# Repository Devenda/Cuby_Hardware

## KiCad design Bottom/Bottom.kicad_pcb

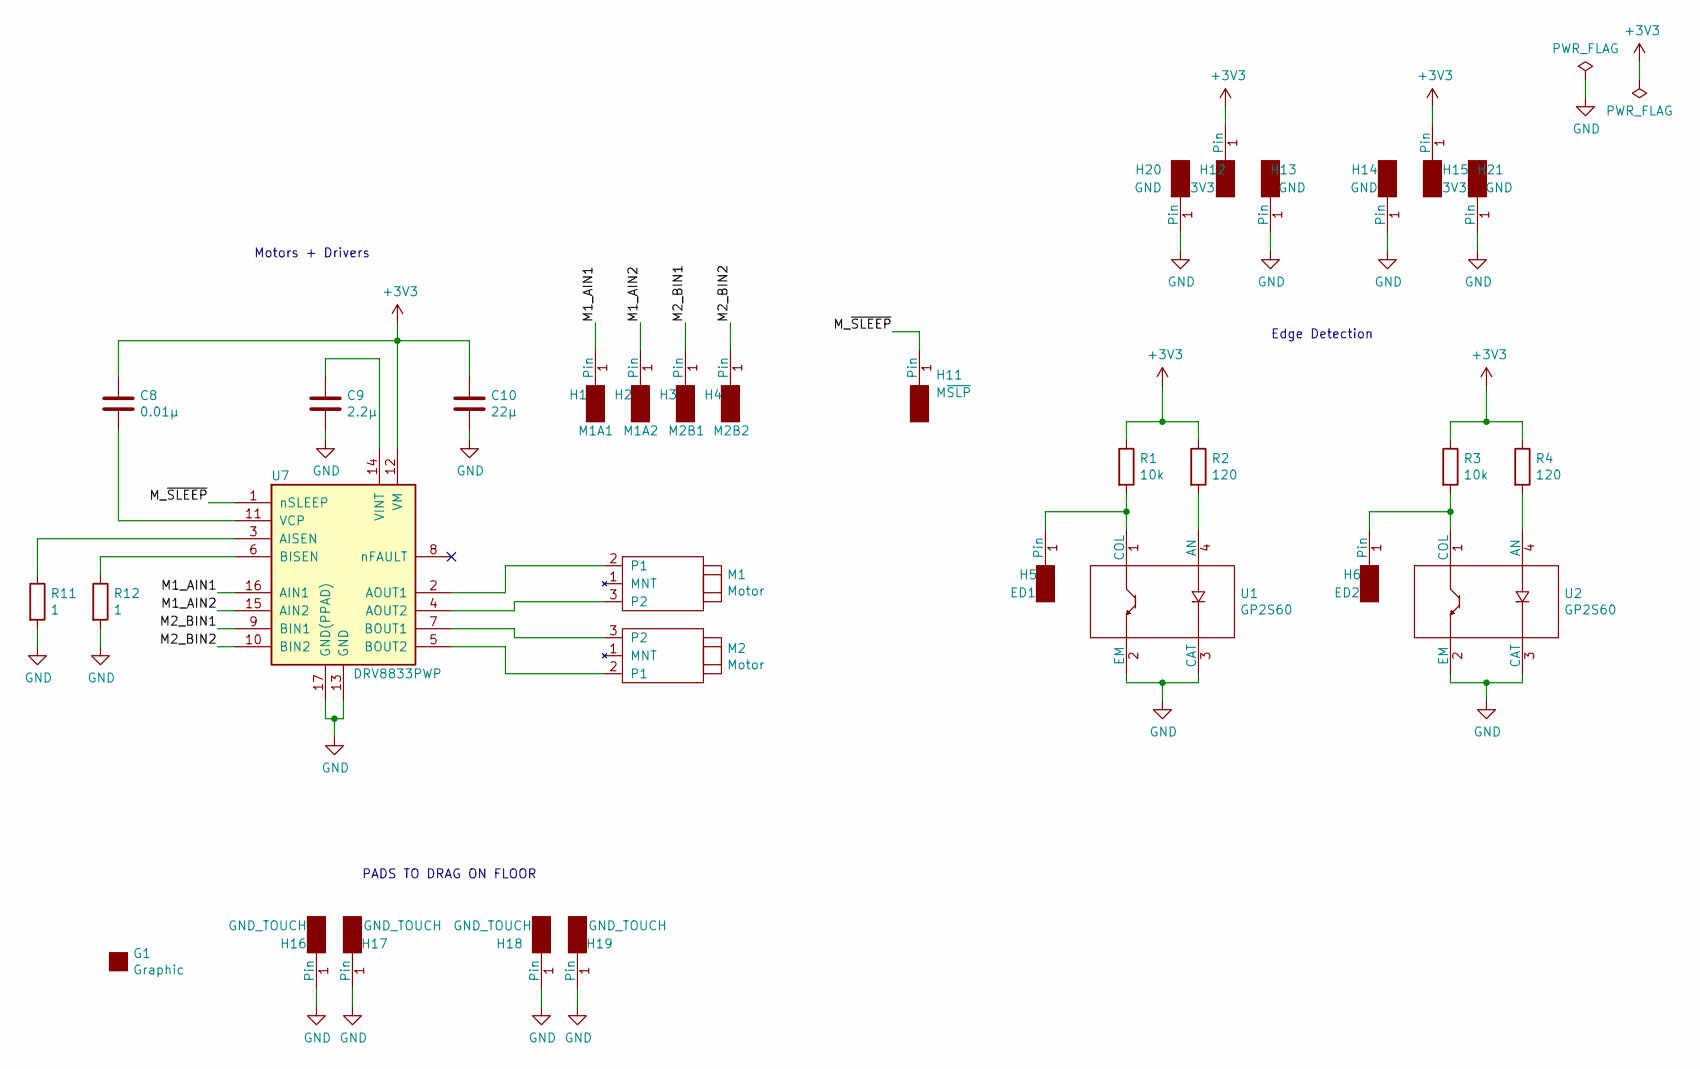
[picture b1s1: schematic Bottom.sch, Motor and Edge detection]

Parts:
C8: 0.01µ; C_0805_2012Metric; LCSC C52278
C9: 2.2µ; C_0805_2012Metric; LCSC C107171
C10: 22µ; C_0805_2012Metric; LCSC C5674
G1: Graphic; d2
H1: M1A1; Mounting_Pad_Signal
H2: M1A2; Mounting_Pad_Signal
H3: M2B1; Mounting_Pad_Signal
H4: M2B2; Mounting_Pad_Signal
H5: ED1; Mounting_Pad_Signal
H6: ED2; Mounting_Pad_Signal
H11: M~SLP; Mounting_Pad_Signal
H12, H15: 3V3; Mounting_Pad_Power
H13, H14, H20, H21: GND; Mounting_Pad_Power
H16, H17, H18, H19: GND_TOUCH; Mounting_Pad_Ground
M1, M2: Motor; Small_DC_Motor
R1, R3: 10k; R_0805_2012Metric; LCSC C38522
R2, R4: 120; R_0805_2012Metric; LCSC C25281
R11, R12: 1; R_0805_2012Metric; LCSC C25288
U1, U2: GP2S60; GP2S60_ReverseMount; LCSC C83485
U7: DRV8833PWP; HTSSOP-16-1EP_4.4x5mm_P0.65mm_EP3.4x5mm_Mask2.46x2.31mm_The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; Farnell 2057085RL

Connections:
+3V3: C8.1, C10.1, H12.1, H15.1, R1.1, R2.1, R3.1, R4.1, U7.12 (VM)
/M1_AIN1: H1.1, U7.16 (AIN1)
/M1_AIN2: H2.1, U7.15 (AIN2)
/M2_BIN1: H3.1, U7.9 (BIN1)
/M2_BIN2: H4.1, U7.10 (BIN2)
/M_~SLEEP: H11.1, U7.1 (nSLEEP)
GND: C9.2, C10.2, H13.1, H14.1, H16.1, H17.1, H18.1, H19.1, H20.1, H21.1, R11.2, R12.2, U1.2 (EM), U1.3 (CAT), U2.2 (EM), U2.3 (CAT), U7.13 (GND), U7.17 (GND(PPAD))
unnamed: C8.2, U7.11 (VCP)
unnamed: C9.1, U7.14 (VINT)
unnamed: H5.1, R1.2, U1.1 (COL)
unnamed: H6.1, R3.2, U2.1 (COL)
unnamed: M1.2 (P1), U7.2 (AOUT1)
unnamed: M1.3 (P2), U7.4 (AOUT2)
unnamed: M2.2 (P1), U7.5 (BOUT2)
unnamed: M2.3 (P2), U7.7 (BOUT1)
unnamed: R2.2, U1.4 (AN)
unnamed: R4.2, U2.4 (AN)
unnamed: R11.1, U7.3 (AISEN)
unnamed: R12.1, U7.6 (BISEN)

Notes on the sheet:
Motors + Drivers
Edge Detection
PADS TO DRAG ON FLOOR

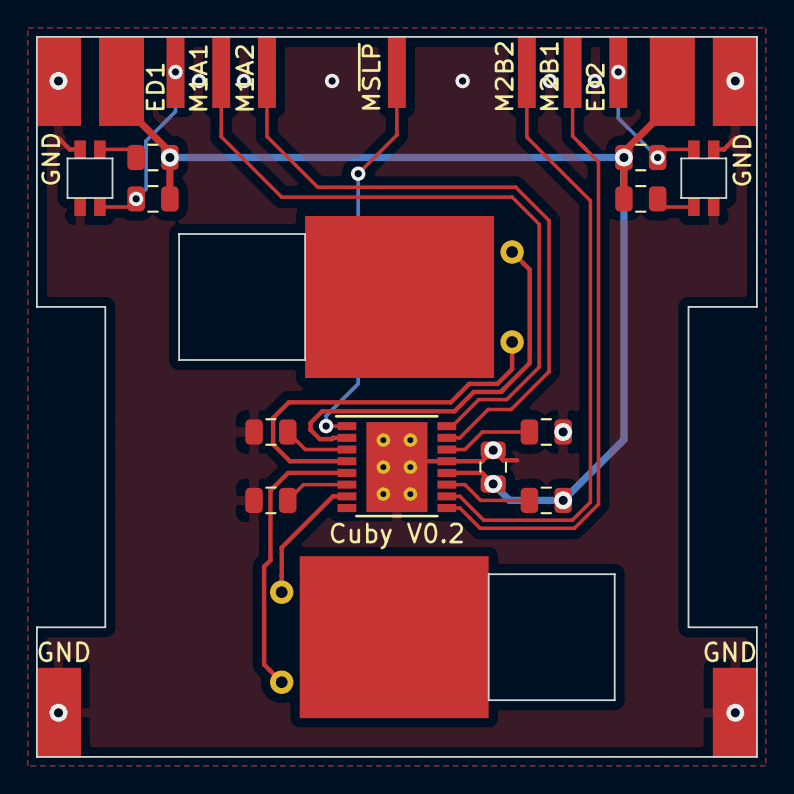
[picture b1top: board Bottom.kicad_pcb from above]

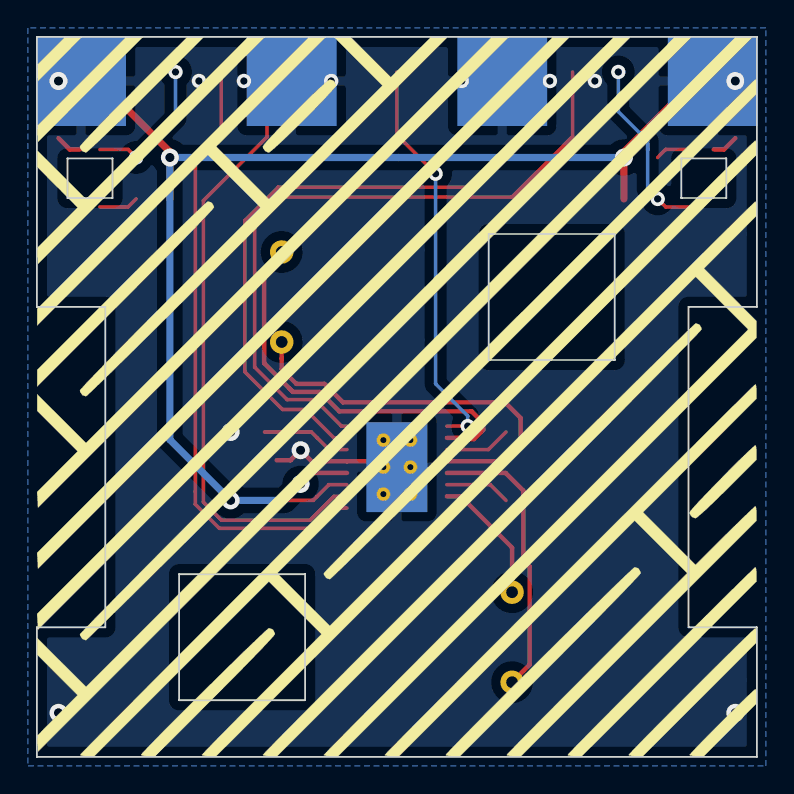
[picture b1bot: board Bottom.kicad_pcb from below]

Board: 2 copper layers, 40.0 x 40.0 mm, 32 parts (5 on the bottom side), 19 nets.

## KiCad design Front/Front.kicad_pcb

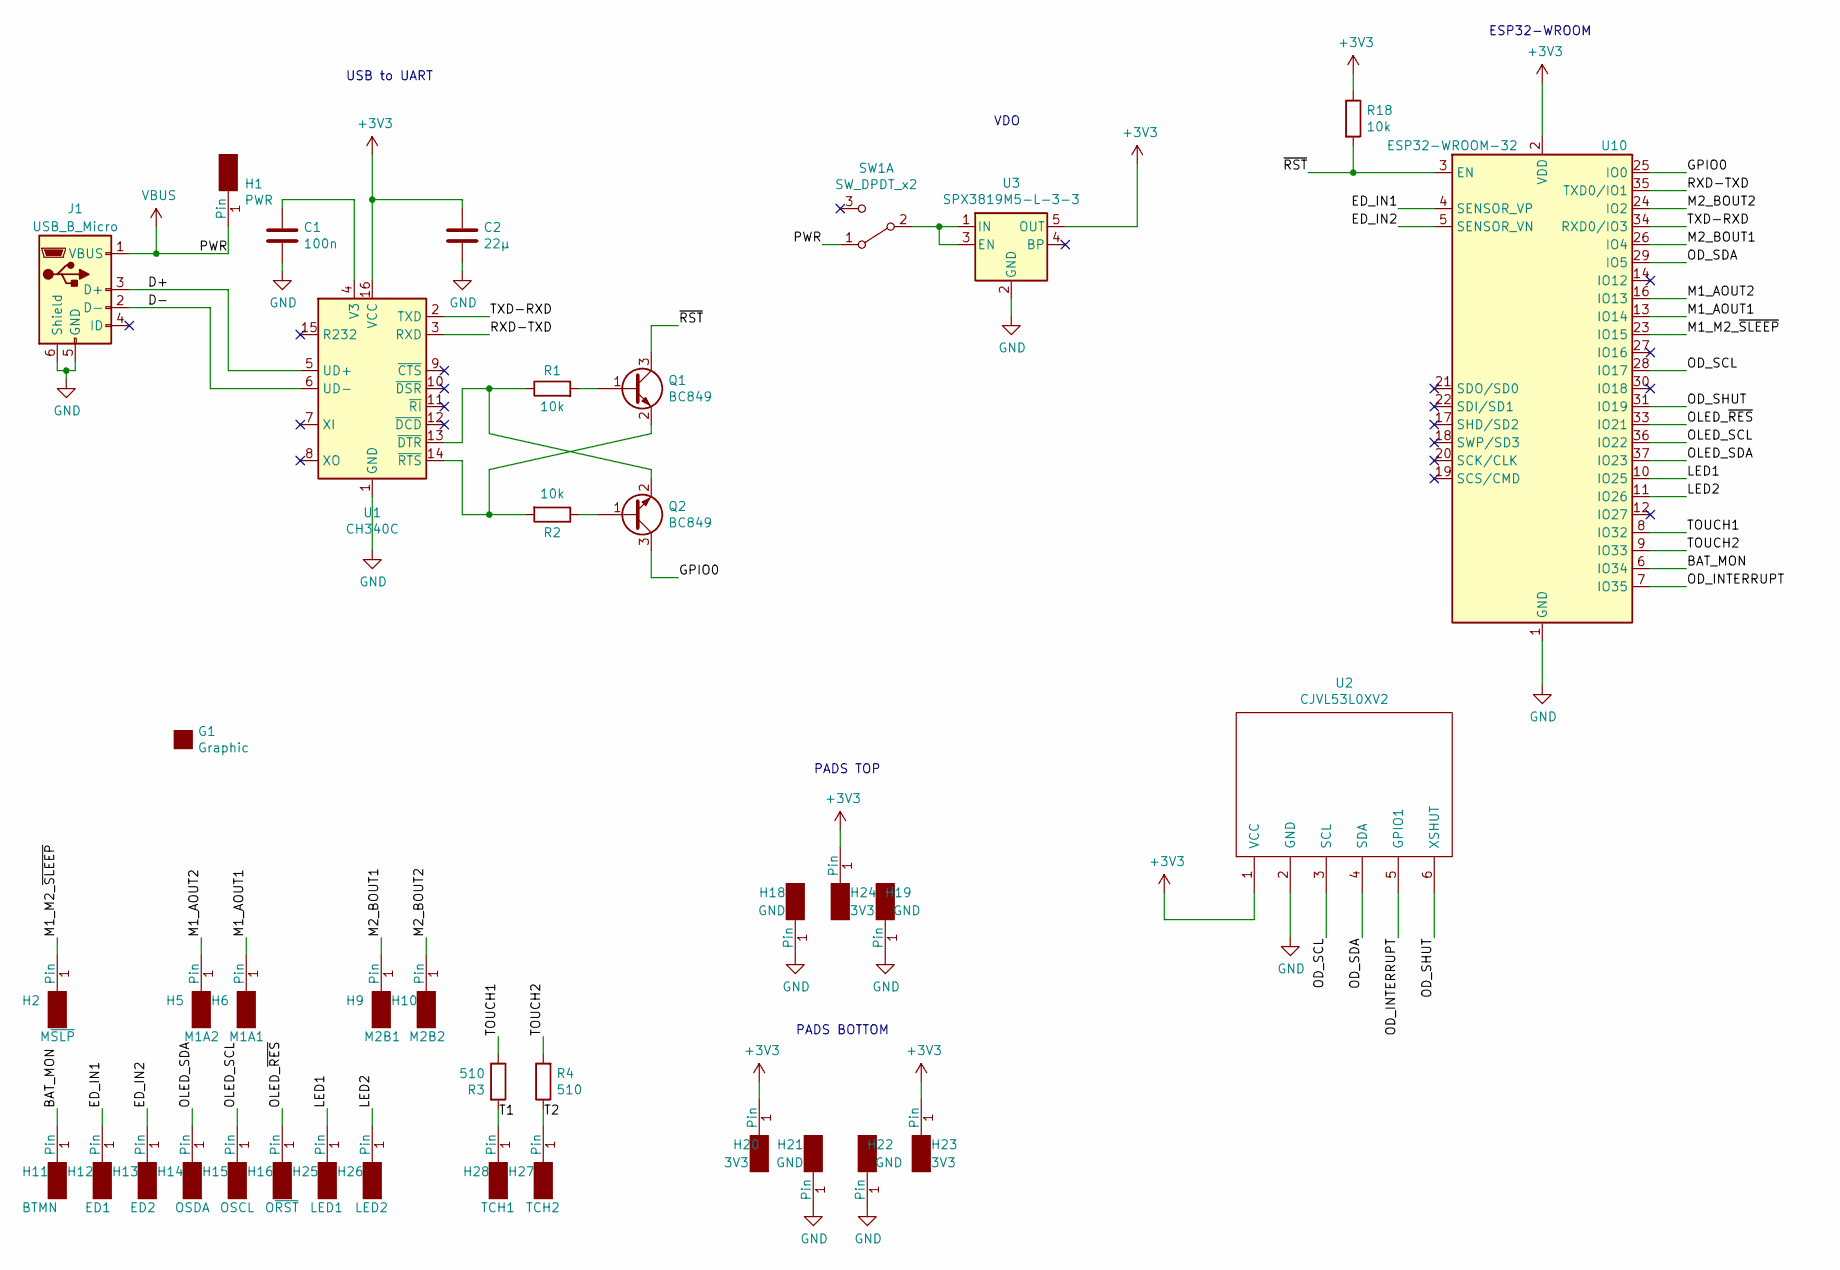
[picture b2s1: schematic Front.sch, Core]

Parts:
C1: 100n; C_0805_2012Metric; LCSC C282732
C2: 22µ; C_0805_2012Metric; LCSC C5674
G1: Graphic; d1
H1: PWR; Mounting_Pad_Power
H2: M~SLP; Mounting_Pad_Signal
H5: M1A2; Mounting_Pad_Signal
H6: M1A1; Mounting_Pad_Signal
H9: M2B1; Mounting_Pad_Signal
H10: M2B2; Mounting_Pad_Signal
H11: BTMN; Mounting_Pad_Signal
H12: ED1; Mounting_Pad_Signal
H13: ED2; Mounting_Pad_Signal
H14: OSDA; Mounting_Pad_Signal
H15: OSCL; Mounting_Pad_Signal
H16: O~RST; Mounting_Pad_Signal
H18, H19, H21, H22: GND; Mounting_Pad_Power
H20, H23, H24: 3V3; Mounting_Pad_Power
H25: LED1; Mounting_Pad_Signal
H26: LED2; Mounting_Pad_Signal
H27: TCH2; Mounting_Pad_Touch
H28: TCH1; Mounting_Pad_Touch
J1: USB_B_Micro; USB_Micro-B_Molex_47346-0001; LCSC C40942
Q1, Q2: BC849; SOT-23; LCSC C163753
R1, R2, R18: 10k; R_0805_2012Metric; LCSC C38522
R3, R4: 510; R_0805_2012Metric; LCSC C25283
SW1: SW_DPDT_x2; JS102011SAQN
U1: CH340C; SOIC-16_3.9x9.9mm_P1.27mm; LCSC C84681
U2: CJVL53L0XV2; GYVL53L0X_NoMountingHoles
U3: SPX3819M5-L-3-3; SOT-23-5; LCSC C9055
U10: ESP32-WROOM-32

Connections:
+3V3: C2.1, H20.1, H23.1, H24.1, R18.1, U1.16 (VCC), U2.1 (VCC), U3.5 (OUT), U10.2 (VDD)
/BAT_MON: H11.1, U10.6 (IO34)
/D+: J1.3 (D+), U1.5 (UD+)
/D-: J1.2 (D-), U1.6 (UD-)
/ED_IN1: H12.1, U10.4 (SENSOR_VP)
/ED_IN2: H13.1, U10.5 (SENSOR_VN)
/GPIO0: Q2.3 (C), U10.25 (IO0)
/LED1: H25.1, U10.10 (IO25)
/LED2: H26.1, U10.11 (IO26)
/M1_AOUT1: H6.1, U10.13 (IO14)
/M1_AOUT2: H5.1, U10.16 (IO13)
/M1_M2_~SLEEP: H2.1, U10.23 (IO15)
/M2_BOUT1: H9.1, U10.26 (IO4)
/M2_BOUT2: H10.1, U10.24 (IO2)
/OD_INTERRUPT: U2.5 (GPIO1), U10.7 (IO35)
/OD_SCL: U2.3 (SCL), U10.28 (IO17)
/OD_SDA: U2.4 (SDA), U10.29 (IO5)
/OD_SHUT: U2.6 (XSHUT), U10.31 (IO19)
/OLED_SCL: H15.1, U10.36 (IO22)
/OLED_SDA: H14.1, U10.37 (IO23)
/OLED_~RES: H16.1, U10.33 (IO21)
/RXD-TXD: U1.3 (RXD), U10.35 (TXD0/IO1)
/T1: H28.1, R3.2
/T2: H27.1, R4.1
/TOUCH1: R3.1, U10.8 (IO32)
/TOUCH2: R4.2, U10.9 (IO33)
/TXD-RXD: U1.2 (TXD), U10.34 (RXD0/IO3)
/~RST: Q1.3 (C), R18.2, U10.3 (EN)
GND: C1.2, C2.2, H18.1, H19.1, H21.1, H22.1, J1.5 (GND), J1.6 (Shield), U1.1 (GND), U2.2 (GND), U3.2 (GND), U10.1 (GND), U10.15 (GND), U10.38 (GND)
unnamed: C1.1, U1.4 (V3)
unnamed: Q1.1 (B), R1.2
unnamed: Q1.2 (E), R2.2, U1.14 (~RTS)
unnamed: Q2.1 (B), R2.1
unnamed: Q2.2 (E), R1.1, U1.13 (~DTR)
unnamed: SW1.2 (B), U3.1 (IN), U3.3 (EN)
VBUS: H1.1, J1.1 (VBUS), SW1.1 (A)

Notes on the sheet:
ESP32-WROOM
USB to UART
VDO
PADS BOTTOM
PADS TOP

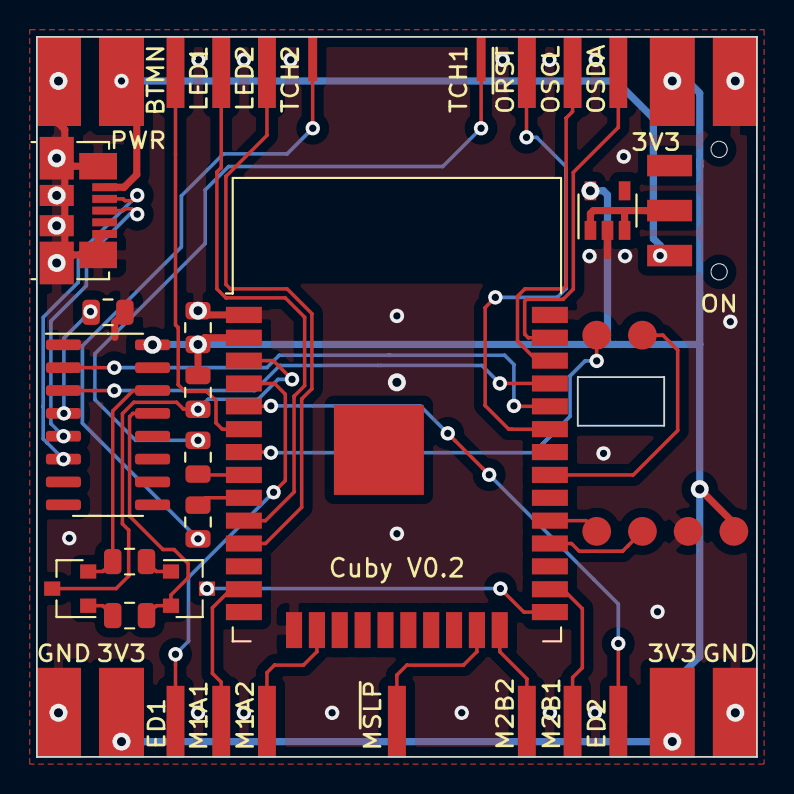
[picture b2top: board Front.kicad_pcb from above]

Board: 2 copper layers, 40.0 x 40.0 mm, 39 parts (1 on the bottom side), 36 nets.

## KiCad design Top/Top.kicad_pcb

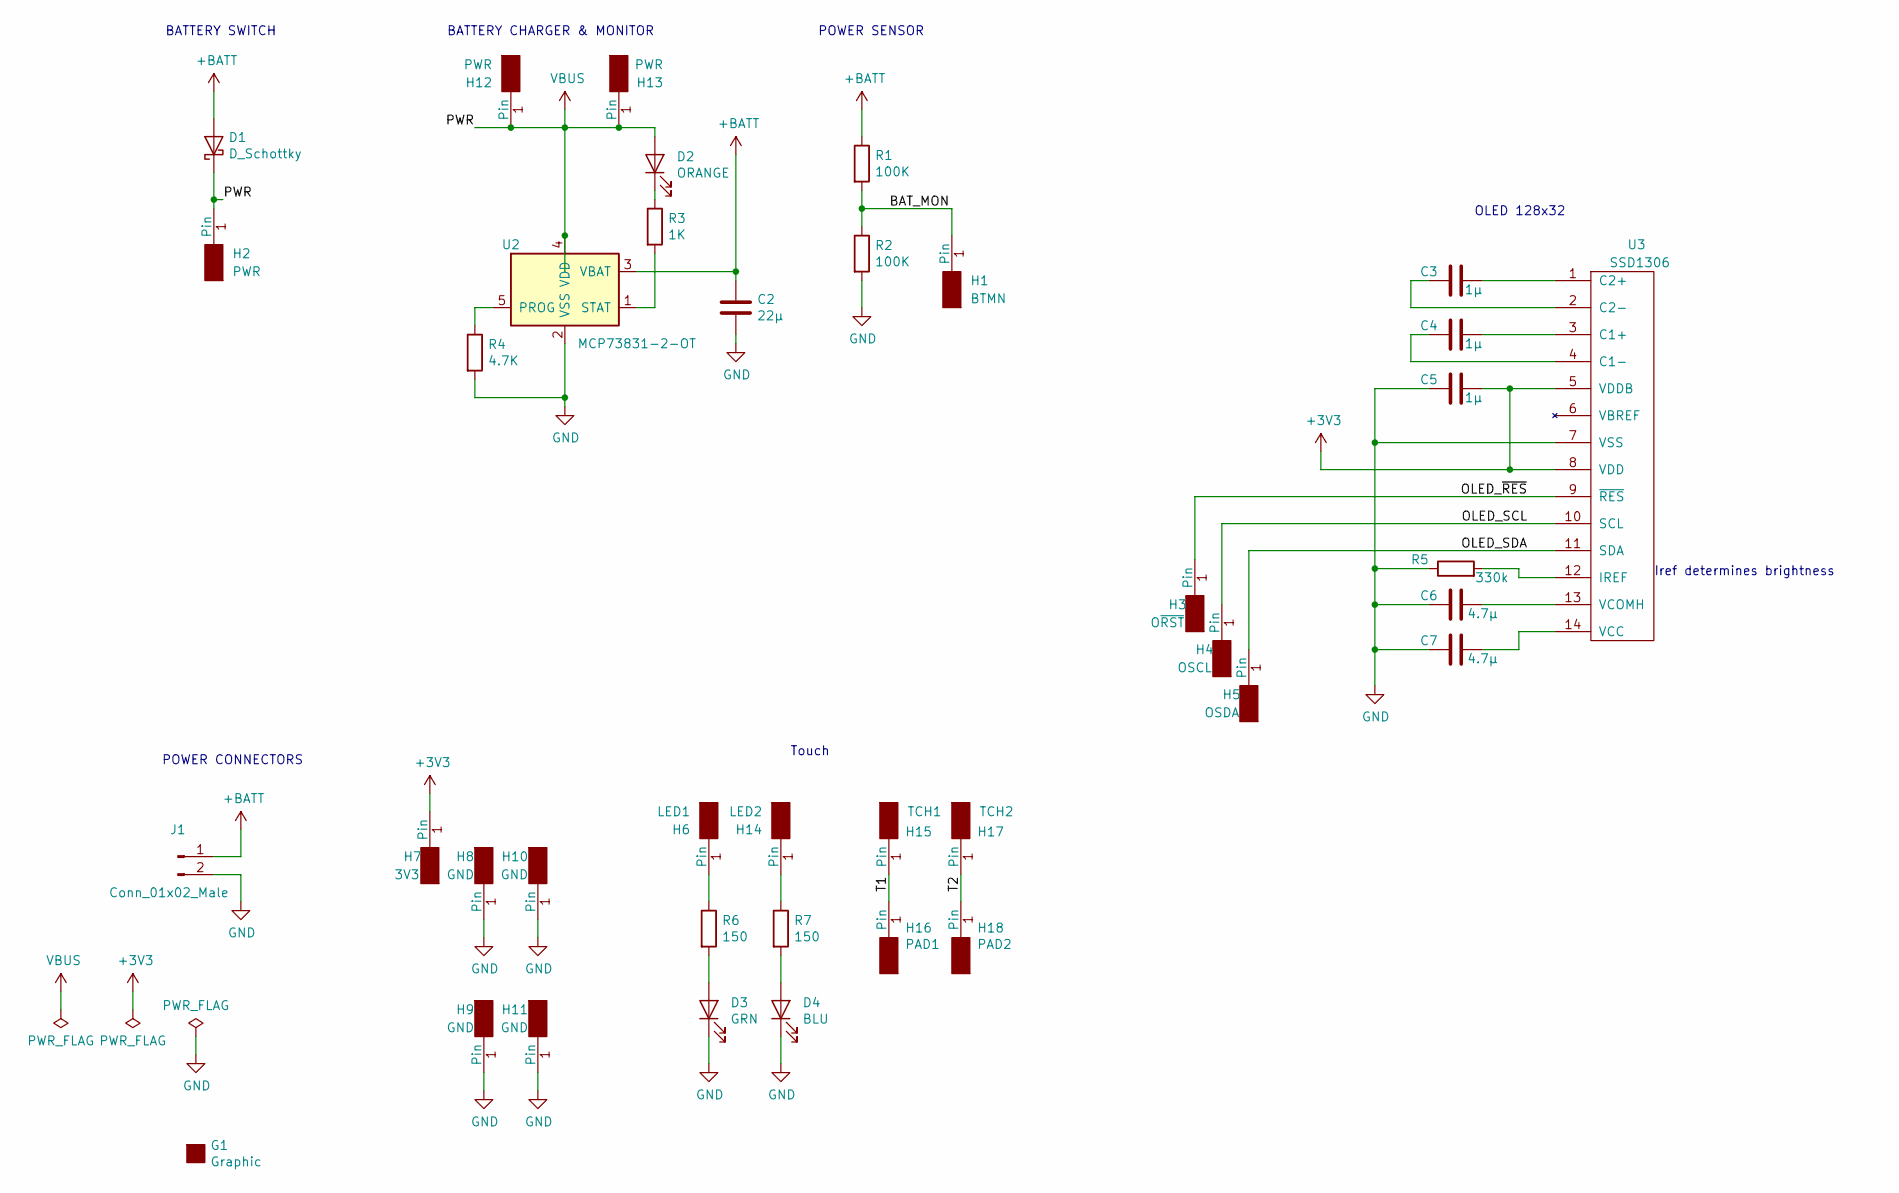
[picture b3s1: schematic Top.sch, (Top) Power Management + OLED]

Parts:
C2: 22µ; C_0805_2012Metric; LCSC C5674
C3, C4, C5: 1µ; C_0805_2012Metric; LCSC C106837
C6, C7: 4.7µ; C_0805_2012Metric; LCSC C87998
D1: D_Schottky; D_SOD-123; LCSC C181204
D2: ORANGE; LED_0805_2012Metric; LCSC C84269
D3: GRN; LED_0805_2012Metric
D4: BLU; LED_0805_2012Metric
G1: Graphic; d3
H1: BTMN; Mounting_Pad_Signal
H2, H12, H13: PWR; Mounting_Pad_Power
H3: O~RST; Mounting_Pad_Signal
H4: OSCL; Mounting_Pad_Signal
H5: OSDA; Mounting_Pad_Signal
H6: LED1; Mounting_Pad_Signal
H7: 3V3; Mounting_Pad_Power
H8, H9, H10, H11: GND; Mounting_Pad_Power
H14: LED2; Mounting_Pad_Signal
H15: TCH1; Mounting_Pad_Touch
H16: PAD1; Touch_Pad
H17: TCH2; Mounting_Pad_Touch
H18: PAD2; Touch_Pad
J1: Conn_01x02_Male; Conn_Bat
R1, R2: 100K; R_0805_2012Metric; LCSC C25611
R3: 1K; R_0805_2012Metric; LCSC C25623
R4: 4.7K; R_0805_2012Metric; LCSC C26022
R5: 330k; R_0805_2012Metric; LCSC C17629
R6, R7: 150; R_0805_2012Metric; LCSC C26022
U2: MCP73831-2-OT; SOT-23-5; LCSC C14879
U3: SSD1306; SSD1306_OLED

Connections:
+3V3: C5.1, H7.1, U3.5 (VDDB), U3.8 (VDD)
+BATT: C2.1, D1.2 (A), J1.1, R1.1, U2.3 (VBAT)
/BAT_MON: H1.1, R1.2, R2.1
/OLED_SCL: H4.1, U3.10 (SCL)
/OLED_SDA: H5.1, U3.11 (SDA)
/OLED_~RES: H3.1, U3.9 (~RES)
/T1: H15.1, H16.1
/T2: H17.1, H18.1
GND: C2.2, C5.2, C6.2, C7.1, D3.1 (K), D4.1 (K), H8.1, H9.1, H10.1, H11.1, J1.2, R2.2, R4.2, R5.1, U2.2 (VSS), U3.7 (VSS)
unnamed: C3.1, U3.1 (C2+)
unnamed: C3.2, U3.2 (C2-)
unnamed: C4.1, U3.3 (C1+)
unnamed: C4.2, U3.4 (C1-)
unnamed: C6.1, U3.13 (VCOMH)
unnamed: C7.2, U3.14 (VCC)
unnamed: D2.1 (K), R3.1
unnamed: D3.2 (A), R6.2
unnamed: D4.2 (A), R7.2
unnamed: H6.1, R6.1
unnamed: H14.1, R7.1
unnamed: R3.2, U2.1 (STAT)
unnamed: R4.1, U2.5 (PROG)
unnamed: R5.2, U3.12 (IREF)
VBUS: D1.1 (K), D2.2 (A), H2.1, H12.1, H13.1, U2.4 (VDD)

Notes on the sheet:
BATTERY CHARGER & MONITOR
POWER SENSOR
POWER CONNECTORS
OLED 128x32
Iref determines brightness
BATTERY SWITCH
Touch

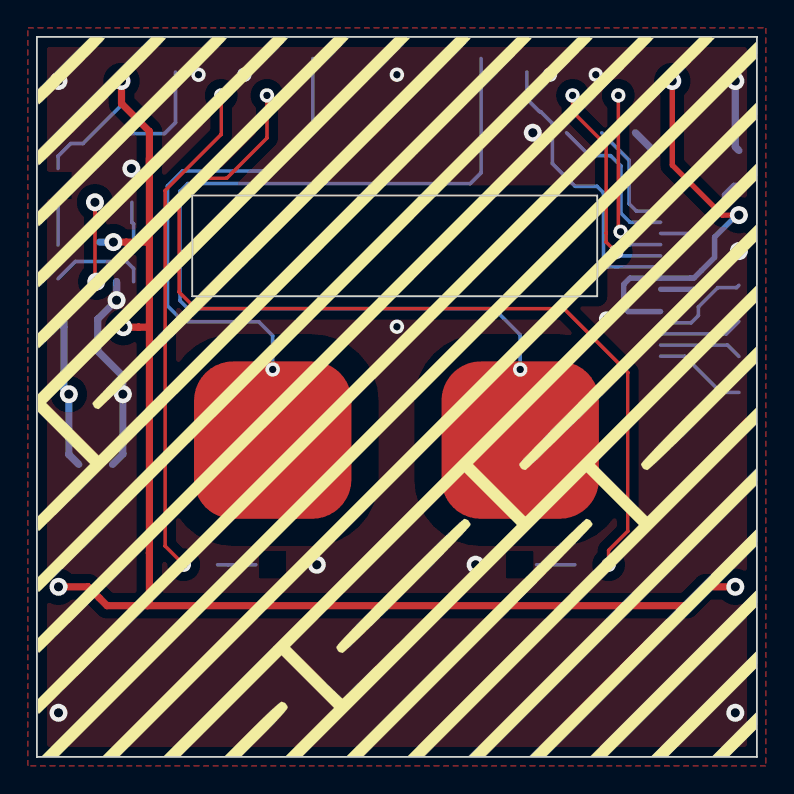
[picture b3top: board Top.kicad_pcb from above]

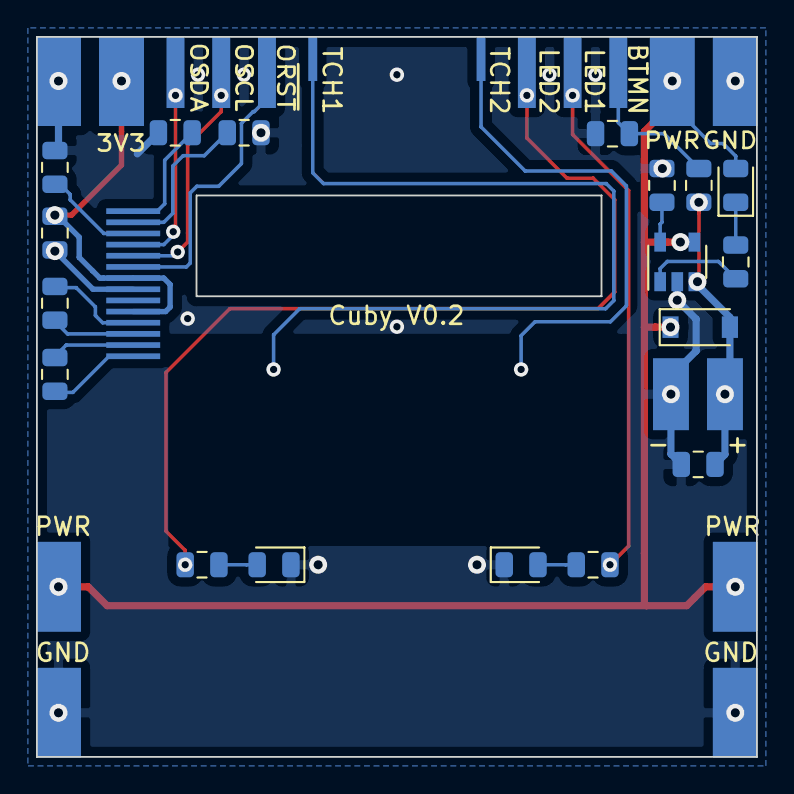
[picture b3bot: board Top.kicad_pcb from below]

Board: 2 copper layers, 40.0 x 40.0 mm, 39 parts (36 on the bottom side), 24 nets.

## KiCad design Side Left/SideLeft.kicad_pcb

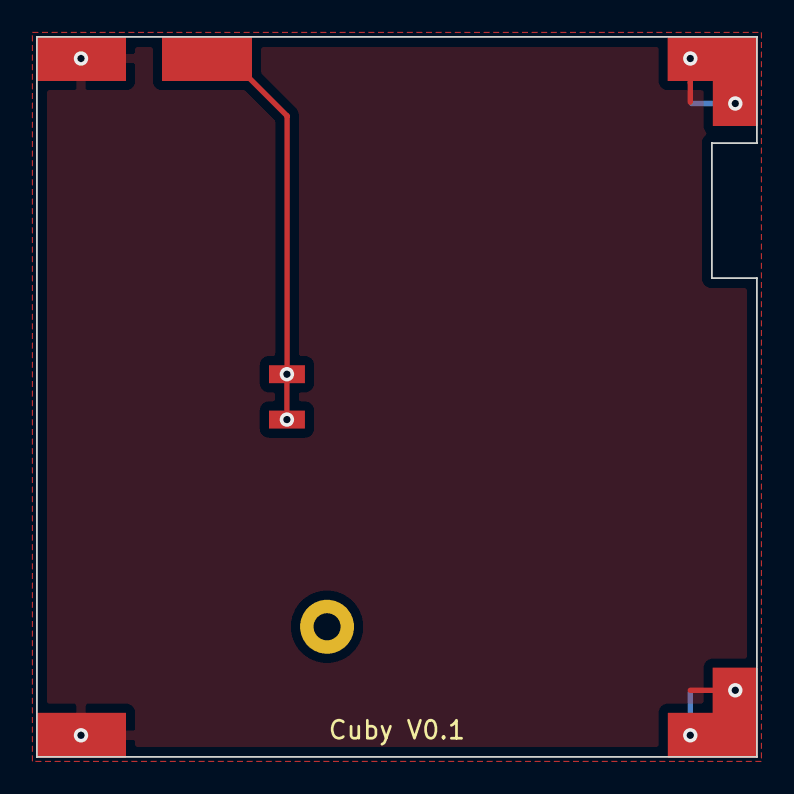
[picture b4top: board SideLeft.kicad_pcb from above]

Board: 2 copper layers, 40.0 x 40.0 mm, 7 parts (0 on the bottom side), 2 nets.

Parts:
H2, H3: GND; Mounting_Pad_Power
H5, H7: GND; Mounting_Pad_Power_Corner
H10: VBS; Mounting_Pad_Power
J1: Conn_01x01; Axis
J3: Conn_01x02; BG300-02-A-L-A

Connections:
/VBUS: H10.1, J3.1, J3.2
GND: H2.1, H3.1, H5.1, H7.1

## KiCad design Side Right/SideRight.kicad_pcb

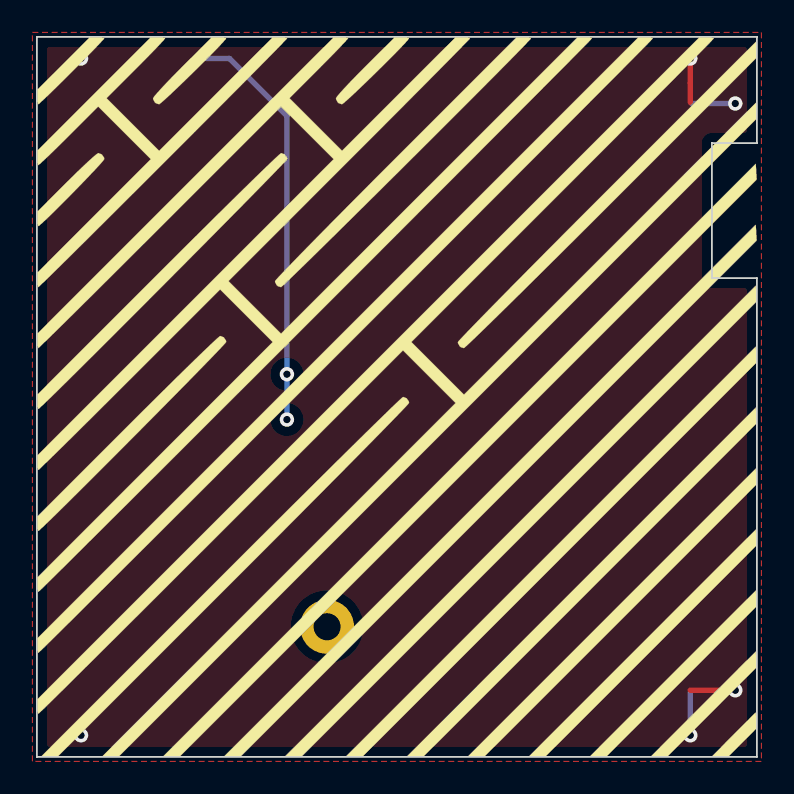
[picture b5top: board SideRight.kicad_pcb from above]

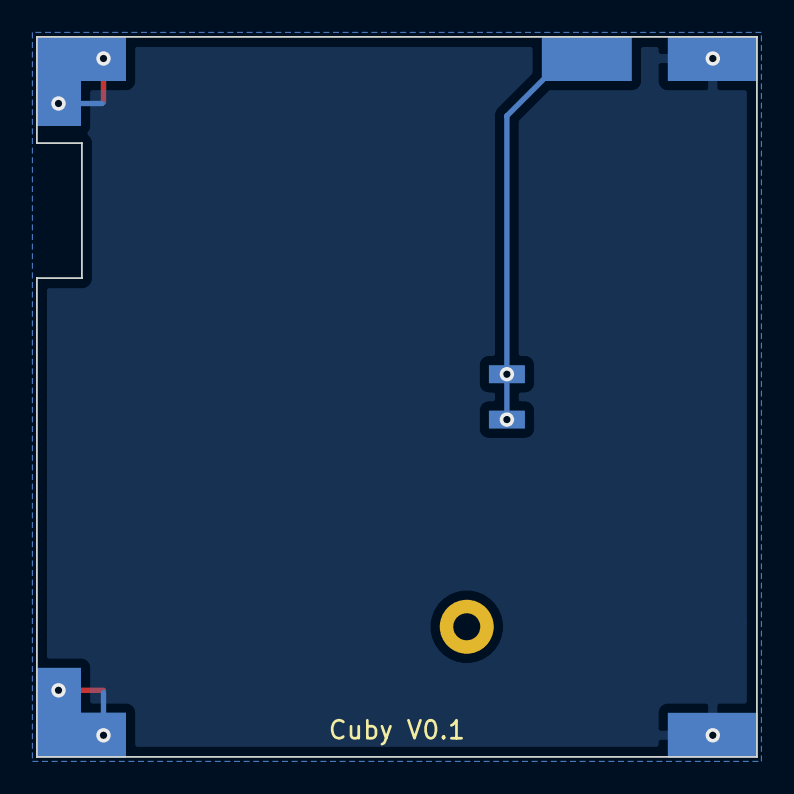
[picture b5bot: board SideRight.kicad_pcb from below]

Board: 2 copper layers, 40.0 x 40.0 mm, 7 parts (6 on the bottom side), 2 nets.

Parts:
H1, H4: GND; Mounting_Pad_Power
H6, H8: GND; Mounting_Pad_Power_Corner
H12: VBS; Mounting_Pad_Power
J1: Conn_01x01; Axis
J2: Conn_01x02; BG300-02-A-L-A

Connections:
/VBUS: H12.1, J2.1, J2.2
GND: H1.1, H4.1, H6.1, H8.1

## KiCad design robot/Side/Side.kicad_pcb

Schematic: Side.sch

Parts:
H1, H2, H3, H4: GND; Mounting_Pad_Power
H5, H6, H7, H8: GND; Mounting_Pad_Power_Corner
H10, H12: VBS; Mounting_Pad_Power
J1: Conn_01x01; Axis
J2, J3: Conn_01x02; BG300-02-A-L-A

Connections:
/VBUS: H10.1, H12.1, J2.1, J2.2, J3.1, J3.2
GND: H1.1, H2.1, H3.1, H4.1, H5.1, H6.1, H7.1, H8.1

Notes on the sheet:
Corners
VBUS

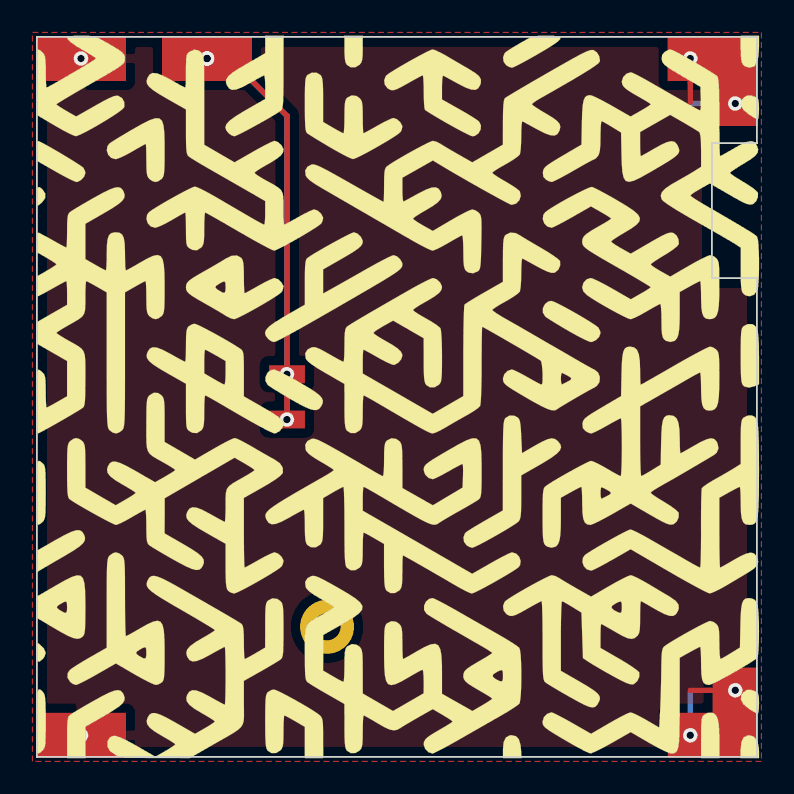
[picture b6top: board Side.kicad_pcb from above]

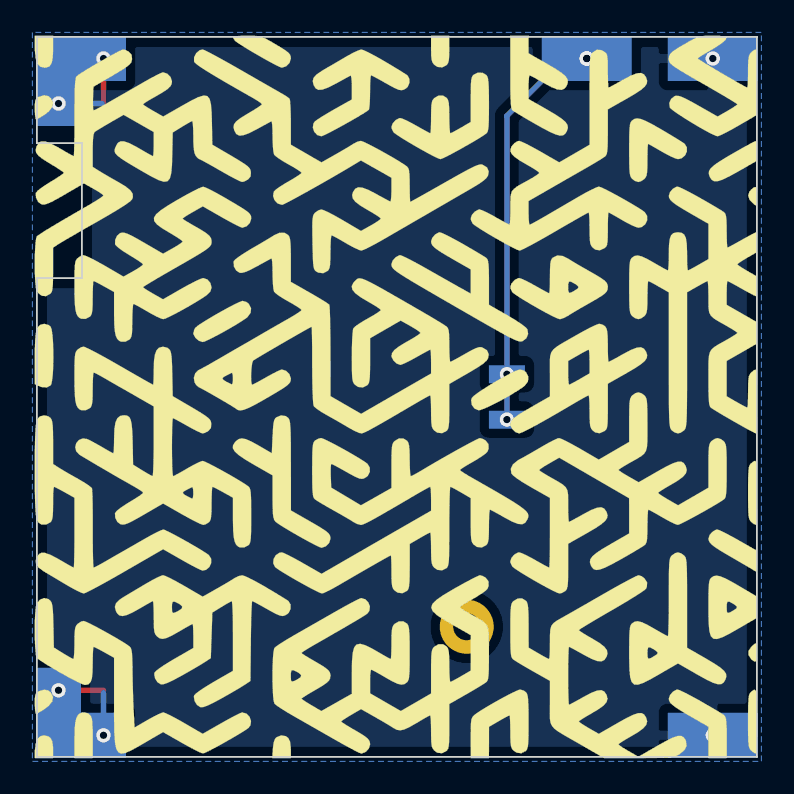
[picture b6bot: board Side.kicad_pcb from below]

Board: 2 copper layers, 40.0 x 40.0 mm, 13 parts (6 on the bottom side), 2 nets.

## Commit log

2019-06-28 Initial
2019-06-28 Added Project base
2019-06-30 Power management
2019-07-02 USB to UART + autoreset
2019-07-16 added new core, changes to USBToUART
2019-08-25 Object detection, reset
2019-08-25 Edge Detection, start Motor and Driver
2019-08-30 Motor driver
2019-08-30 UI parts, (re)wiring remaining signals
2019-09-01 DRC check fixes and small changes
2019-09-01 Testpoints, switch, small changes
2019-09-02 annotations, testpoints, small changes
2019-09-06 Restructure project
    Removed sub sheets and made 'sub' project all in the same folder
2019-09-08 Cleanup, start PDB Front
2019-09-10 Front PCB
2019-09-11 Front Routing
2019-09-12 Finish Front
2019-09-13 Top PCB
2019-09-13 Swap 3V3 and VBUS, Fix Cutout, small changes
2019-09-13 Silkscreen Top
2019-09-16 Bottom
2019-09-16 Start renumber
2019-09-16 Renumber and more Bottom
2019-09-18 Finish bottom
2019-09-19 Bottem changes
2019-09-21 Shrink design
2019-09-22 Finish Front redesign
2019-09-22 Finish Top, remap OLED pins
2019-09-22 Finisch bottom
2019-09-25 Changes to bottom, 3D export
2019-09-26 Small fixes, step files
2019-09-26 Small changes to top, step
2019-09-27 Move Motors
2019-09-29 Layout changes, new footprints, added Side PCB
2019-10-02 Changes to structure
2019-10-02 Top changes
2019-10-02 Update footprints
2019-10-03 Small changes, connectors
2019-10-06 Add VBS, Add Silk deco, small changes
2019-10-11 Small changes, BOM, Gerbers
2019-10-11 BOM items
2019-10-11 Restructure
2019-11-18 Changes to motor on bottom: fix mirrored pins
2019-11-23 V0.2: Redo front schematic and PCB
2019-11-30 updated bottom (motor placement, sharp sensor), front redesign, start op top redesign
2019-12-02 Update Top V0.2, small changes to motor placement
2019-12-03 finish top, changes to front, added graphic
2019-12-04 finishing touches, moved touch traces to back
2019-12-17 Small DC motor
2019-12-18 Bottom, new motor, positioning and start routing
2019-12-20 removed extra pins in front, respaced pins in bottom and front
